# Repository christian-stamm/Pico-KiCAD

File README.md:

# Pico-KiCAD

The **DebugProbe** project aims to re-imagine Raspberry Pi Debug Probe.

## Anke (Debug Probe)

**Anke** is a 4-layer board intended to accommodate the popular Raspberry Pi RP2040 MCU with all required component to function identically to Raspberry Pi Debug Probe. The board is pin-compatible with Raspberry Pi Debug Probe and can be used with the same picoprobe SW.

Features:

- Very small form-factor of about 25x40mm.
- Raspberry Pi RP2040 MCU as a heart of the board.
- USB Type-C connector for power and communication.
- Several LEDs to indicate power and status.
- BOOTSEL button to enter the bootloader mode for flashing new picoprobe SW.
- Pin-compatible with Raspberry Pi Debug Probe.

## Bernd (RGB Panel ECU)

Bernd is a 4-layer board intended to drive 4x2 RGB Panels each consisting of 64x64 Pixel.

Features:

- Very small form-factor of about 60x60mm.
- Raspberry Pi RP2350B MCU as a heart of the board.
- USB Type-C connector for power and communication.
- BOOTSEL button to enter the bootloader mode for flashing new picoprobe SW.

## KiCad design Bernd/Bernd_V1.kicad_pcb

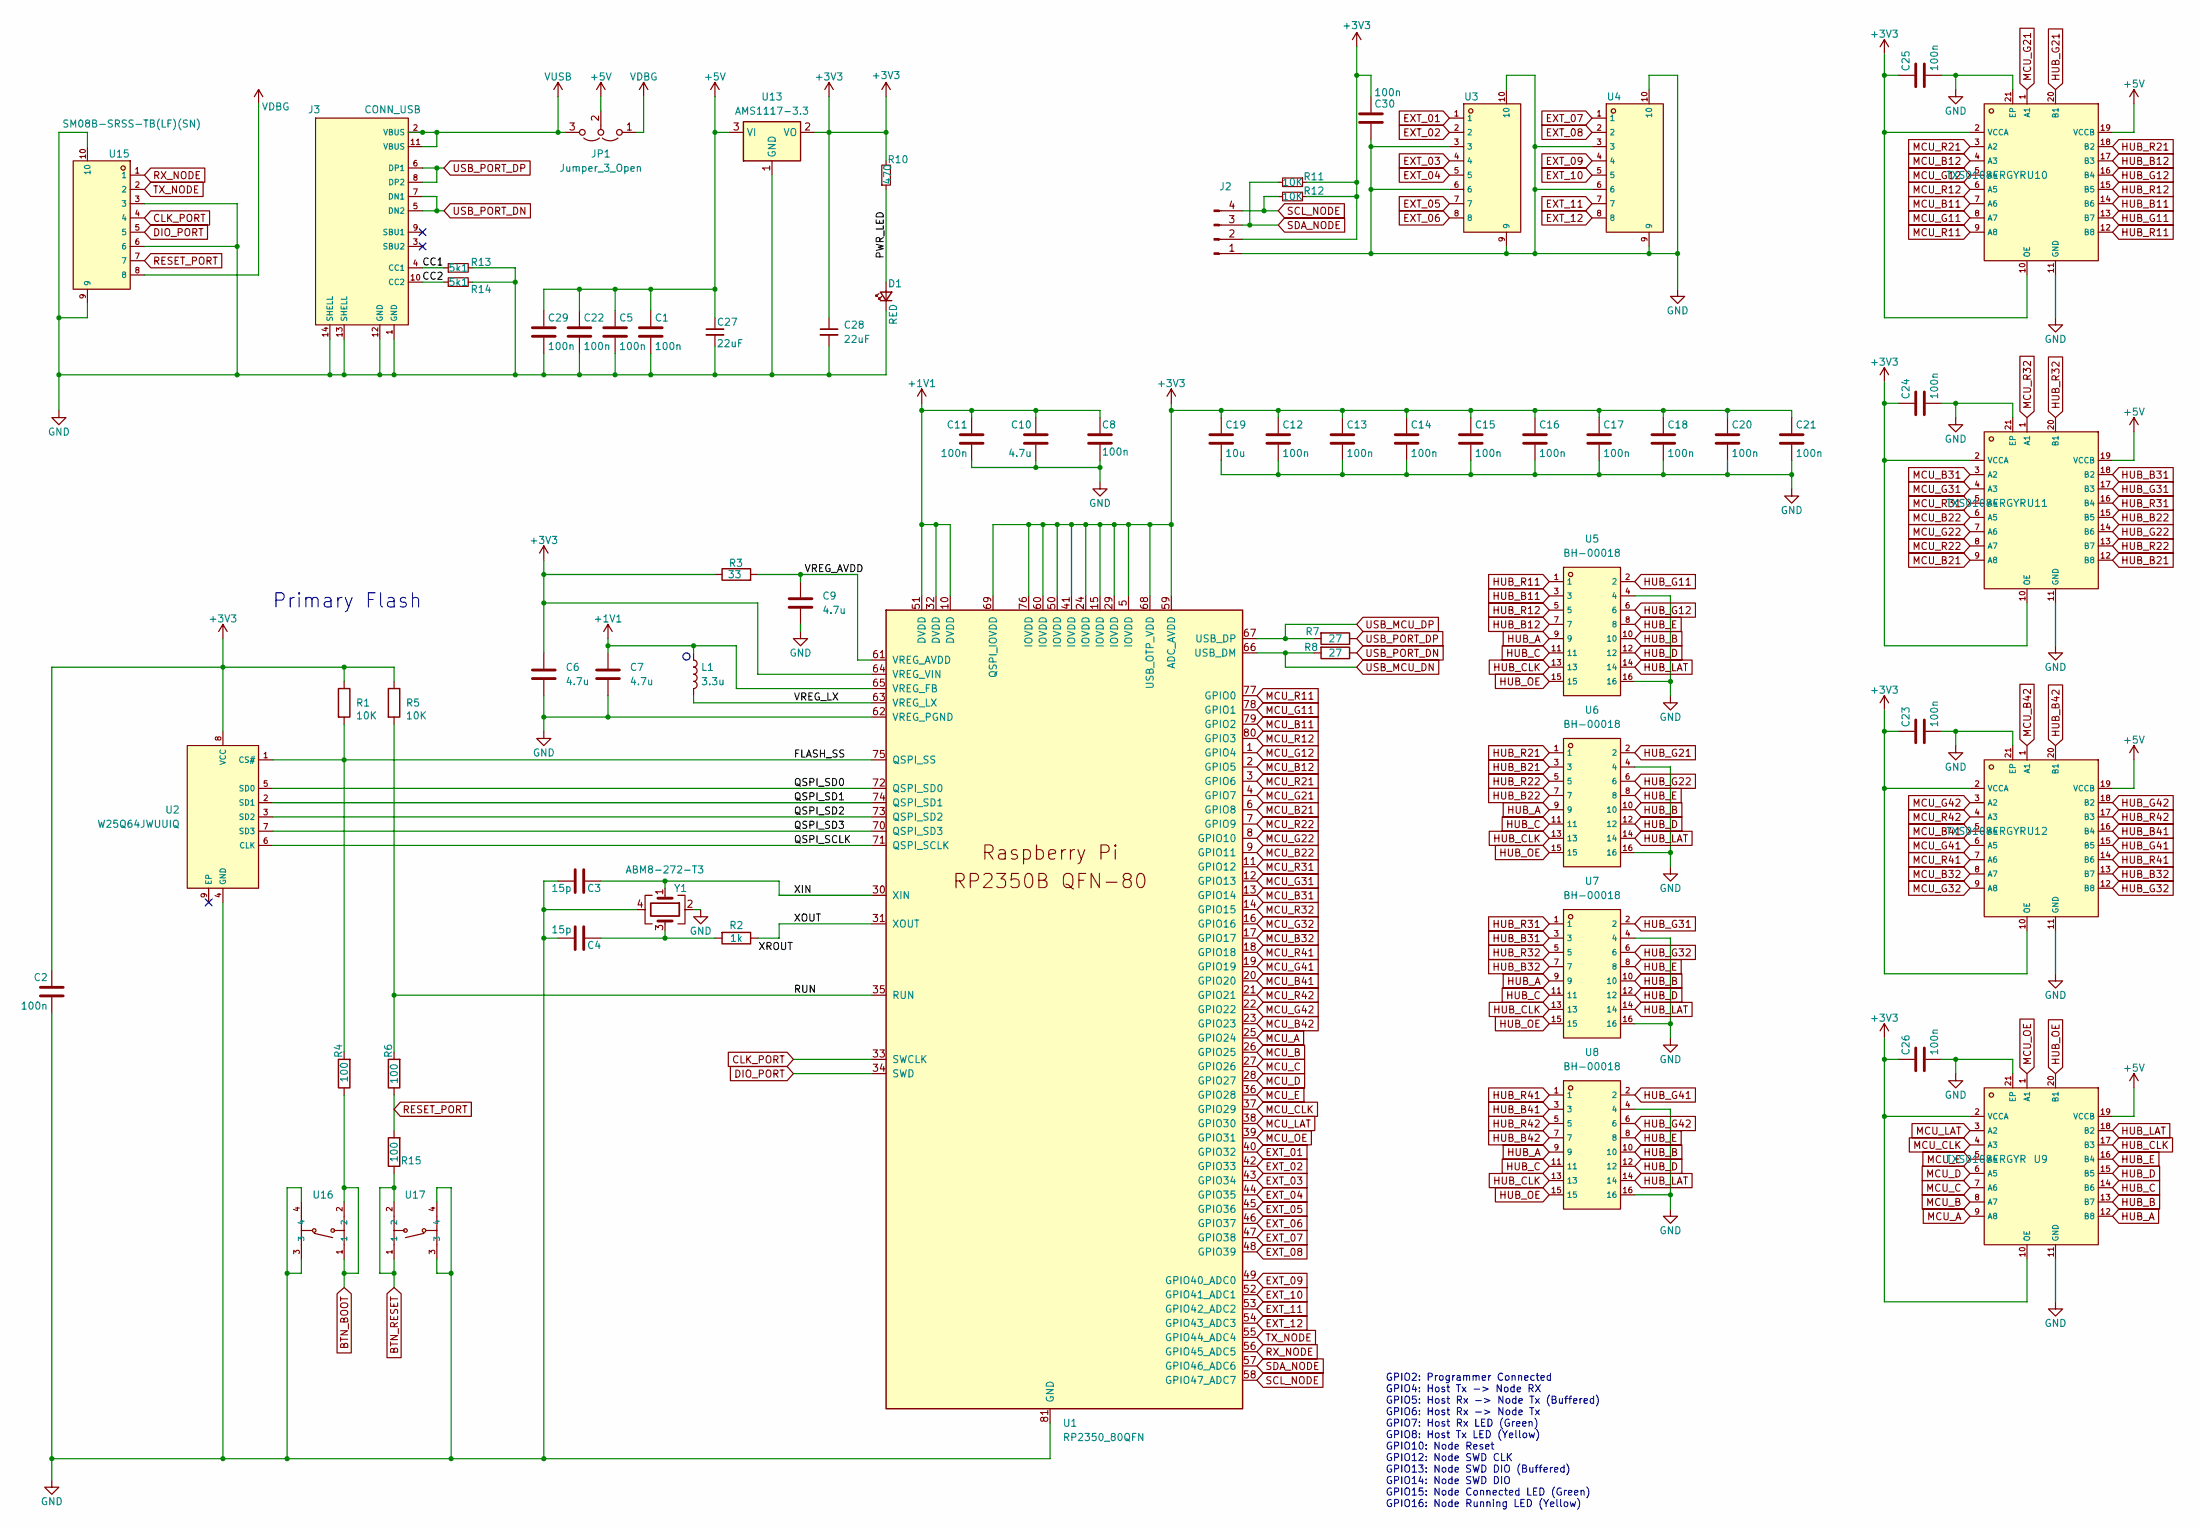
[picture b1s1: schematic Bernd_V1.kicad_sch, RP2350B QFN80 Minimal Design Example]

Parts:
C1, C2, C5, C8, C11, C12, C13, C14, C15, C16, C17, C18, C20, C21, C22, C23, C24, C25, C26, C29, C30: 100n; C_0402_1005Metric
C3, C4: 15p; C_0402_1005Metric
C6, C7: 4.7u; R_0402_1005Metric
C9, C10: 4.7u; C_0402_1005Metric
C19: 10u; C_0402_1005Metric
C27, C28: 22uF; C_0603_1608Metric; LCSC C45783
D1: RED; LED_0603_1608Metric; LCSC C2286
J2: Conn_01x04_Pin; JST_SH_BM04B-SRSS-TB_1x04-1MP_P1.00mm_Vertical; LCSC C160390
J3: CONN_USB; USB-C-SMD_TYPE-C-6PIN-2MD-073; LCSC C2765186
JP1: Jumper_3_Open; PinHeader_1x03_P2.54mm_Vertical_SMD_Pin1Left
L1: 3.3u; IND-SMD_L2.0-W1.6_AOTA-B201610S3R3-101-T
R1, R5: 10K; R_0402_1005Metric
R2: 1k; R_0402_1005Metric
R3: 33; R_0402_1005Metric
R4, R6, R15: 100; R_0402_1005Metric
R7, R8: 27; R_0402_1005Metric
R10: 470; R_0402_1005Metric; LCSC C11702
R11, R12: 10K; R_0402_1005Metric; LCSC C11702
R13, R14: 5k1; R_0402_1005Metric; LCSC C25905
U1: RP2350_80QFN; QFN-80_L10.0-W10.0-P0.40-TL-EP3.4
U2: W25Q64JWUUIQ; USON-8_L3.0-W2.0-P0.50-BL-EP; LCSC C6604692
U3, U4, U15: SM08B-SRSS-TB(LF)(SN); CONN-TH_SM08B-SRSS-TB-LF-SN; LCSC C160407
U5, U6, U7, U8: BH-00018; CONN-SMD_321016MG0CBK00A0; LCSC C2829931
U9, U10, U11, U12: TXS0108ERGYR; VQFN-20_L4.6-W3.6-P0.50-BL-EP; LCSC C90706
U13: AMS1117-3.3; SOT-223-3_TabPin2
U16, U17: TS-1089S-02526; SW-SMD_4P-L4.2-W3.3-P2.15-LS5.1; LCSC C455282
Y1: ABM8-272-T3; CRYSTAL-SMD_4P-L3.2-W2.5-BL

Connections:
+1V1: C7.1, C8.1, C10.1, C11.1, L1.1, U1.10 (DVDD), U1.32 (DVDD), U1.51 (DVDD), U1.65 (VREG_FB)
+3V3: C2.1, C6.1, C12.1, C13.1, C14.1, C15.1, C16.1, C17.1, C18.1, C19.1, C20.1, C21.1, C23.1, C24.1, C25.1, C26.1, C28.1, C30.1, J2.2, R1.1, R3.1, R5.1, R10.2, R11.1, R12.1, U1.5 (IOVDD), U1.15 (IOVDD), U1.24 (IOVDD), U1.29 (IOVDD), U1.41 (IOVDD), U1.50 (IOVDD), U1.59 (ADC_AVDD), U1.60 (IOVDD), U1.64 (VREG_VIN), U1.68 (USB_OTP_VDD), U1.69 (QSPI_IOVDD), U1.76 (IOVDD), U2.8 (VCC), U9.2 (VCCA), U9.10 (OE), U10.2 (VCCA), U10.10 (OE), U11.2 (VCCA), U11.10 (OE), U12.2 (VCCA), U12.10 (OE), U13.2 (VO)
+5V: C1.1, C5.1, C22.1, C27.1, C29.1, JP1.2 (C), U9.19 (VCCB), U10.19 (VCCB), U11.19 (VCCB), U12.19 (VCCB), U13.3 (VI)
/CC1: J3.4 (CC1), R13.1
/CC2: J3.10 (CC2), R14.1
/FLASH_SS: R1.2, R4.2, U1.75 (QSPI_SS), U2.1 (CS#)
/PWR_LED: D1.2 (A), R10.1
/QSPI_SCLK: U1.71 (QSPI_SCLK), U2.6 (CLK)
/QSPI_SD0: U1.72 (QSPI_SD0), U2.5 (SD0)
/QSPI_SD1: U1.74 (QSPI_SD1), U2.2 (SD1)
/QSPI_SD2: U1.73 (QSPI_SD2), U2.3 (SD2)
/QSPI_SD3: U1.70 (QSPI_SD3), U2.7 (SD3)
/RUN: R5.2, R6.2, U1.35 (RUN)
/VREG_AVDD: C9.1, R3.2, U1.61 (VREG_AVDD)
/VREG_LX: L1.2, U1.63 (VREG_LX)
/XIN: C3.1, U1.30 (XIN), Y1.1
/XOUT: R2.1, U1.31 (XOUT)
BTN_BOOT: R4.1, U16.1, U16.2
BTN_RESET: R15.1, U17.1, U17.2
CLK_PORT: U1.33 (SWCLK), U15.4
DIO_PORT: U1.34 (SWD), U15.5
EXT_01: U1.40 (GPIO32), U3.1
EXT_02: U1.42 (GPIO33), U3.2
EXT_03: U1.43 (GPIO34), U3.4
EXT_04: U1.44 (GPIO35), U3.5
EXT_05: U1.45 (GPIO36), U3.7
EXT_06: U1.46 (GPIO37), U3.8
EXT_07: U1.47 (GPIO38), U4.1
EXT_08: U1.48 (GPIO39), U4.2
EXT_09: U1.49 (GPIO40_ADC0), U4.4
EXT_10: U1.52 (GPIO41_ADC1), U4.5
EXT_11: U1.53 (GPIO42_ADC2), U4.7
EXT_12: U1.54 (GPIO43_ADC3), U4.8
GND: C1.2, C2.2, C3.2, C4.2, C5.2, C6.2, C7.2, C8.2, C9.2, C10.2, C11.2, C12.2, C13.2, C14.2, C15.2, C16.2, C17.2, C18.2, C19.2, C20.2, C21.2, C22.2, C23.2, C24.2, C25.2, C26.2, C27.2, C28.2, C29.2, C30.2, D1.1 (K), J2.1, J3.1 (GND), J3.12 (GND), J3.13 (SHELL), J3.14 (SHELL), R13.2, R14.2, U1.62 (VREG_PGND), U1.81 (GND), U2.4 (GND), U3.3, U3.6, U3.9, U3.10, U4.3, U4.6, U4.9, U4.10, U5.4, U5.16, U6.4, U6.16, U7.4, U7.16, U8.4, U8.16, U9.11 (GND), U9.21 (EP), U10.11 (GND), U10.21 (EP), U11.11 (GND), U11.21 (EP), U12.11 (GND), U12.21 (EP), U13.1 (GND), U15.3, U15.6, U15.9, U15.10, U16.3, U16.4, U17.3, U17.4, Y1.2, Y1.4
HUB_A: U5.9, U6.9, U7.9, U8.9, U9.12 (B8)
HUB_B: U5.10, U6.10, U7.10, U8.10, U9.13 (B7)
HUB_B11: U5.3, U10.14 (B6)
HUB_B12: U5.7, U10.17 (B3)
HUB_B21: U6.3, U11.12 (B8)
HUB_B22: U6.7, U11.15 (B5)
HUB_B31: U7.3, U11.18 (B2)
HUB_B32: U7.7, U12.13 (B7)
HUB_B41: U8.3, U12.16 (B4)
HUB_B42: U8.7, U12.20 (B1)
HUB_C: U5.11, U6.11, U7.11, U8.11, U9.14 (B6)
HUB_CLK: U5.13, U6.13, U7.13, U8.13, U9.17 (B3)
HUB_D: U5.12, U6.12, U7.12, U8.12, U9.15 (B5)
HUB_E: U5.8, U6.8, U7.8, U8.8, U9.16 (B4)
HUB_G11: U5.2, U10.13 (B7)
HUB_G12: U5.6, U10.16 (B4)
HUB_G21: U6.2, U10.20 (B1)
HUB_G22: U6.6, U11.14 (B6)
HUB_G31: U7.2, U11.17 (B3)
HUB_G32: U7.6, U12.12 (B8)
HUB_G41: U8.2, U12.15 (B5)
HUB_G42: U8.6, U12.18 (B2)
HUB_LAT: U5.14, U6.14, U7.14, U8.14, U9.18 (B2)
HUB_OE: U5.15, U6.15, U7.15, U8.15, U9.20 (B1)
HUB_R11: U5.1, U10.12 (B8)
HUB_R12: U5.5, U10.15 (B5)
HUB_R21: U6.1, U10.18 (B2)
HUB_R22: U6.5, U11.13 (B7)
HUB_R31: U7.1, U11.16 (B4)
HUB_R32: U7.5, U11.20 (B1)
HUB_R41: U8.1, U12.14 (B6)
HUB_R42: U8.5, U12.17 (B3)
MCU_A: U1.25 (GPIO24), U9.9 (A8)
MCU_B: U1.26 (GPIO25), U9.8 (A7)
MCU_B11: U1.79 (GPIO2), U10.7 (A6)
MCU_B12: U1.2 (GPIO5), U10.4 (A3)
MCU_B21: U1.6 (GPIO8), U11.9 (A8)
MCU_B22: U1.9 (GPIO11), U11.6 (A5)
MCU_B31: U1.13 (GPIO14), U11.3 (A2)
MCU_B32: U1.17 (GPIO17), U12.8 (A7)
MCU_B41: U1.20 (GPIO20), U12.5 (A4)
MCU_B42: U1.23 (GPIO23), U12.1 (A1)
MCU_C: U1.27 (GPIO26), U9.7 (A6)
MCU_CLK: U1.37 (GPIO29), U9.4 (A3)
MCU_D: U1.28 (GPIO27), U9.6 (A5)
MCU_E: U1.36 (GPIO28), U9.5 (A4)
MCU_G11: U1.78 (GPIO1), U10.8 (A7)
MCU_G12: U1.1 (GPIO4), U10.5 (A4)
MCU_G21: U1.4 (GPIO7), U10.1 (A1)
MCU_G22: U1.8 (GPIO10), U11.7 (A6)
MCU_G31: U1.12 (GPIO13), U11.4 (A3)
MCU_G32: U1.16 (GPIO16), U12.9 (A8)
MCU_G41: U1.19 (GPIO19), U12.6 (A5)
MCU_G42: U1.22 (GPIO22), U12.3 (A2)
MCU_LAT: U1.38 (GPIO30), U9.3 (A2)
MCU_OE: U1.39 (GPIO31), U9.1 (A1)
MCU_R11: U1.77 (GPIO0), U10.9 (A8)
MCU_R12: U1.80 (GPIO3), U10.6 (A5)
MCU_R21: U1.3 (GPIO6), U10.3 (A2)
MCU_R22: U1.7 (GPIO9), U11.8 (A7)
MCU_R31: U1.11 (GPIO12), U11.5 (A4)
MCU_R32: U1.14 (GPIO15), U11.1 (A1)
MCU_R41: U1.18 (GPIO18), U12.7 (A6)
MCU_R42: U1.21 (GPIO21), U12.4 (A3)
unnamed: C4.1, R2.2, Y1.3
RESET_PORT: R6.1, R15.2, U15.7
RX_NODE: U1.56 (GPIO45_ADC5), U15.1
SCL_NODE: J2.4, R12.2, U1.58 (GPIO47_ADC7)
SDA_NODE: J2.3, R11.2, U1.57 (GPIO46_ADC6)
TX_NODE: U1.55 (GPIO44_ADC4), U15.2
USB_MCU_DN: R8.2, U1.66 (USB_DM)
USB_MCU_DP: R7.2, U1.67 (USB_DP)
USB_PORT_DN: J3.5 (DN2), J3.7 (DN1), R8.1
USB_PORT_DP: J3.6 (DP1), J3.8 (DP2), R7.1
VDBG: JP1.1 (A), U15.8
VUSB: J3.2 (VBUS), J3.11 (VBUS), JP1.3 (B)

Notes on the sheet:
Primary Flash
GPIO2: Programmer Connected GPIO4: Host Tx -> Node RX GPIO5: Host Rx -> Node Tx (Buffered) GPIO6: Host Rx -> Node Tx GPIO7: Host Rx LED (Green) GPIO8: Host Tx LED (Yellow) GPIO10: Node Reset GPIO12: Node SWD CLK GPIO13: Node SWD DIO (Buffered) GPIO14: Node SWD DIO GPIO15: Node Connected LED (Green)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

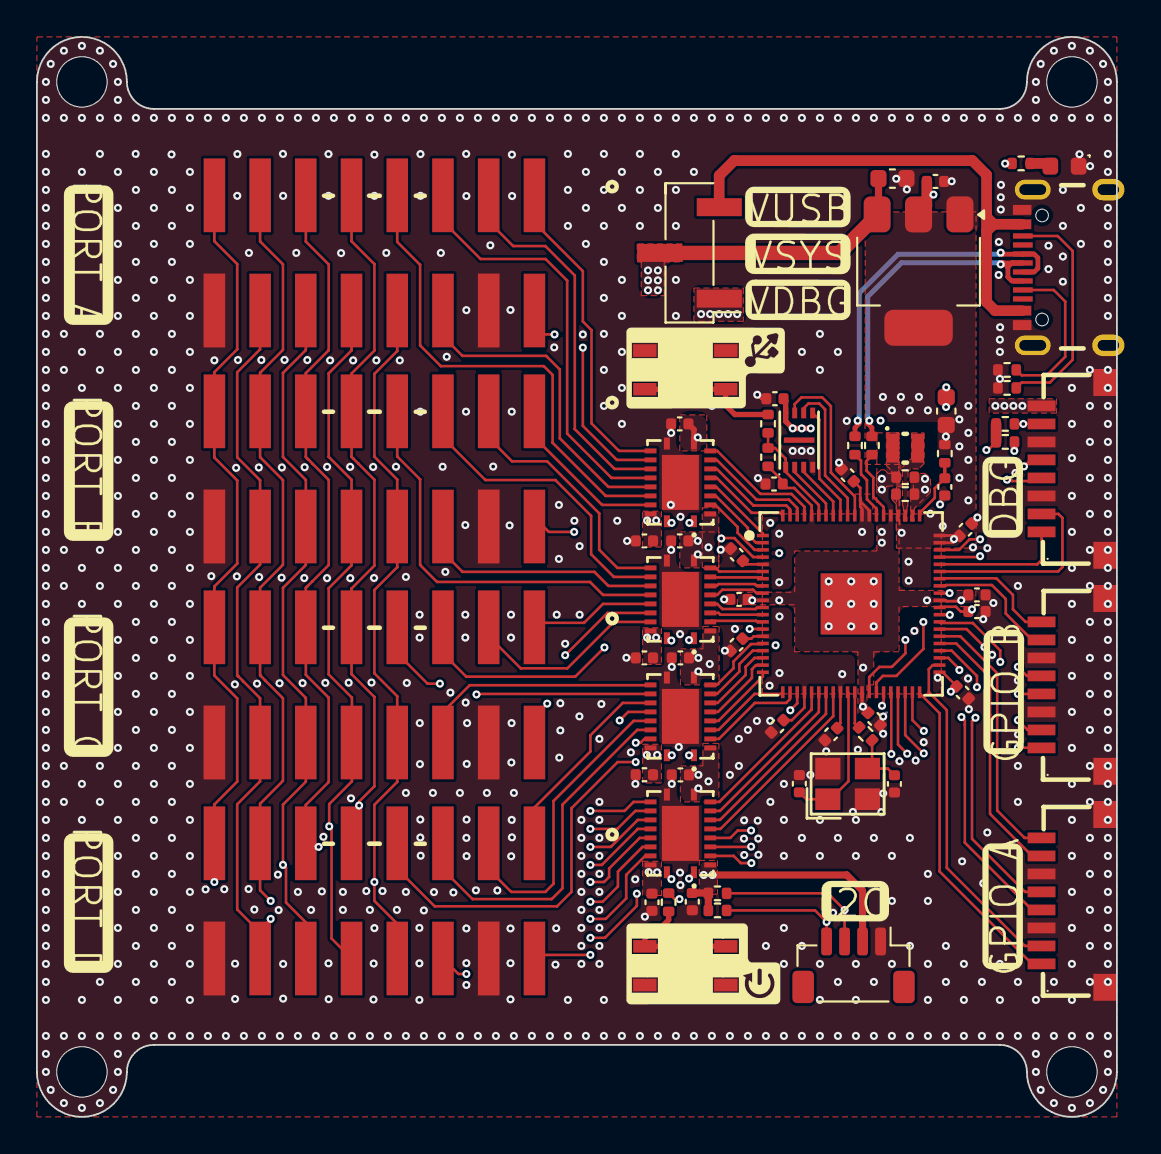
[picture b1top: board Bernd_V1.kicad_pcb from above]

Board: 4 copper layers, 60.0 x 60.0 mm, 66 parts (0 on the bottom side), 110 nets.

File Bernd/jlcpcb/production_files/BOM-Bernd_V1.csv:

Comment,Designator,Footprint,LCSC,Quantity
470,"R10,R11,R12,R2",R_0402_1005Metric,C11702,4
100n,"C1,C11,C12,C13,C14,C15,C16,C17,C18,C2,C20,C21,C22,C23,C24,C25,C26,C29,C30,C5,C8",C_0402_1005Metric,C1525,21
15p,"C3,C4",C_0402_1005Metric,C1548,2
10u,C19,C_0402_1005Metric,C15525,1
Conn_01x04_Pin,J2,JST_SH_BM04B-SRSS-TB_1x04-1MP_P1.00mm_Vertical,C160390,1
SM08B-SRSS-TB(LF)(SN),"U15,U3,U4",CONN-TH_SM08B-SRSS-TB-LF-SN,C160407,3
ABM8-272-T3,Y1,CRYSTAL-SMD_4P-L3.2-W2.5-BL,C20625731,1
RED,D1,LED_0603_1608Metric,C2286,1
4.7u,"C10,C6,C7,C9",C_0402_1005Metric,C23733,4
100,"R15,R4,R6",R_0402_1005Metric,C25076,3
33,R3,R_0402_1005Metric,C25105,1
10K,"R1,R5",R_0402_1005Metric,C25744,2
5k1,"R13,R14",R_0402_1005Metric,C25905,2
CONN_USB,J3,USB-C-SMD_TYPE-C-6PIN-2MD-073,C2765186,1
BH-00018,"U5,U6,U7,U8",CONN-SMD_321016MG0CBK00A0,C2829931,4
3.3u,L1,IND-SMD_L2.0-W1.6_AOTA-B201610S3R3-101-T,C42411119,1
RP2350_80QFN,U1,QFN-80_L10.0-W10.0-P0.40-TL-EP3.4,C42415655,1
TS-1089S-02526,"U16,U17",SW-SMD_4P-L4.2-W3.3-P2.15-LS5.1,C455282,2
22uF,"C27,C28",C_0603_1608Metric,C45783,2
27,"R7,R8",R_0402_1005Metric,C5151586,2
Jumper_3_Open,JP1,PinHeader_1x03_P2.54mm_Vertical_SMD_Pin1Left,C5967212,1
AMS1117-3.3,U13,SOT-223-3_TabPin2,C6186,1
W25Q64JWUUIQ,U2,USON-8_L3.0-W2.0-P0.50-BL-EP,C6604692,1
TXS0108ERGYR,"U10,U11,U12,U9",VQFN-20_L4.6-W3.6-P0.50-BL-EP,C90706,4

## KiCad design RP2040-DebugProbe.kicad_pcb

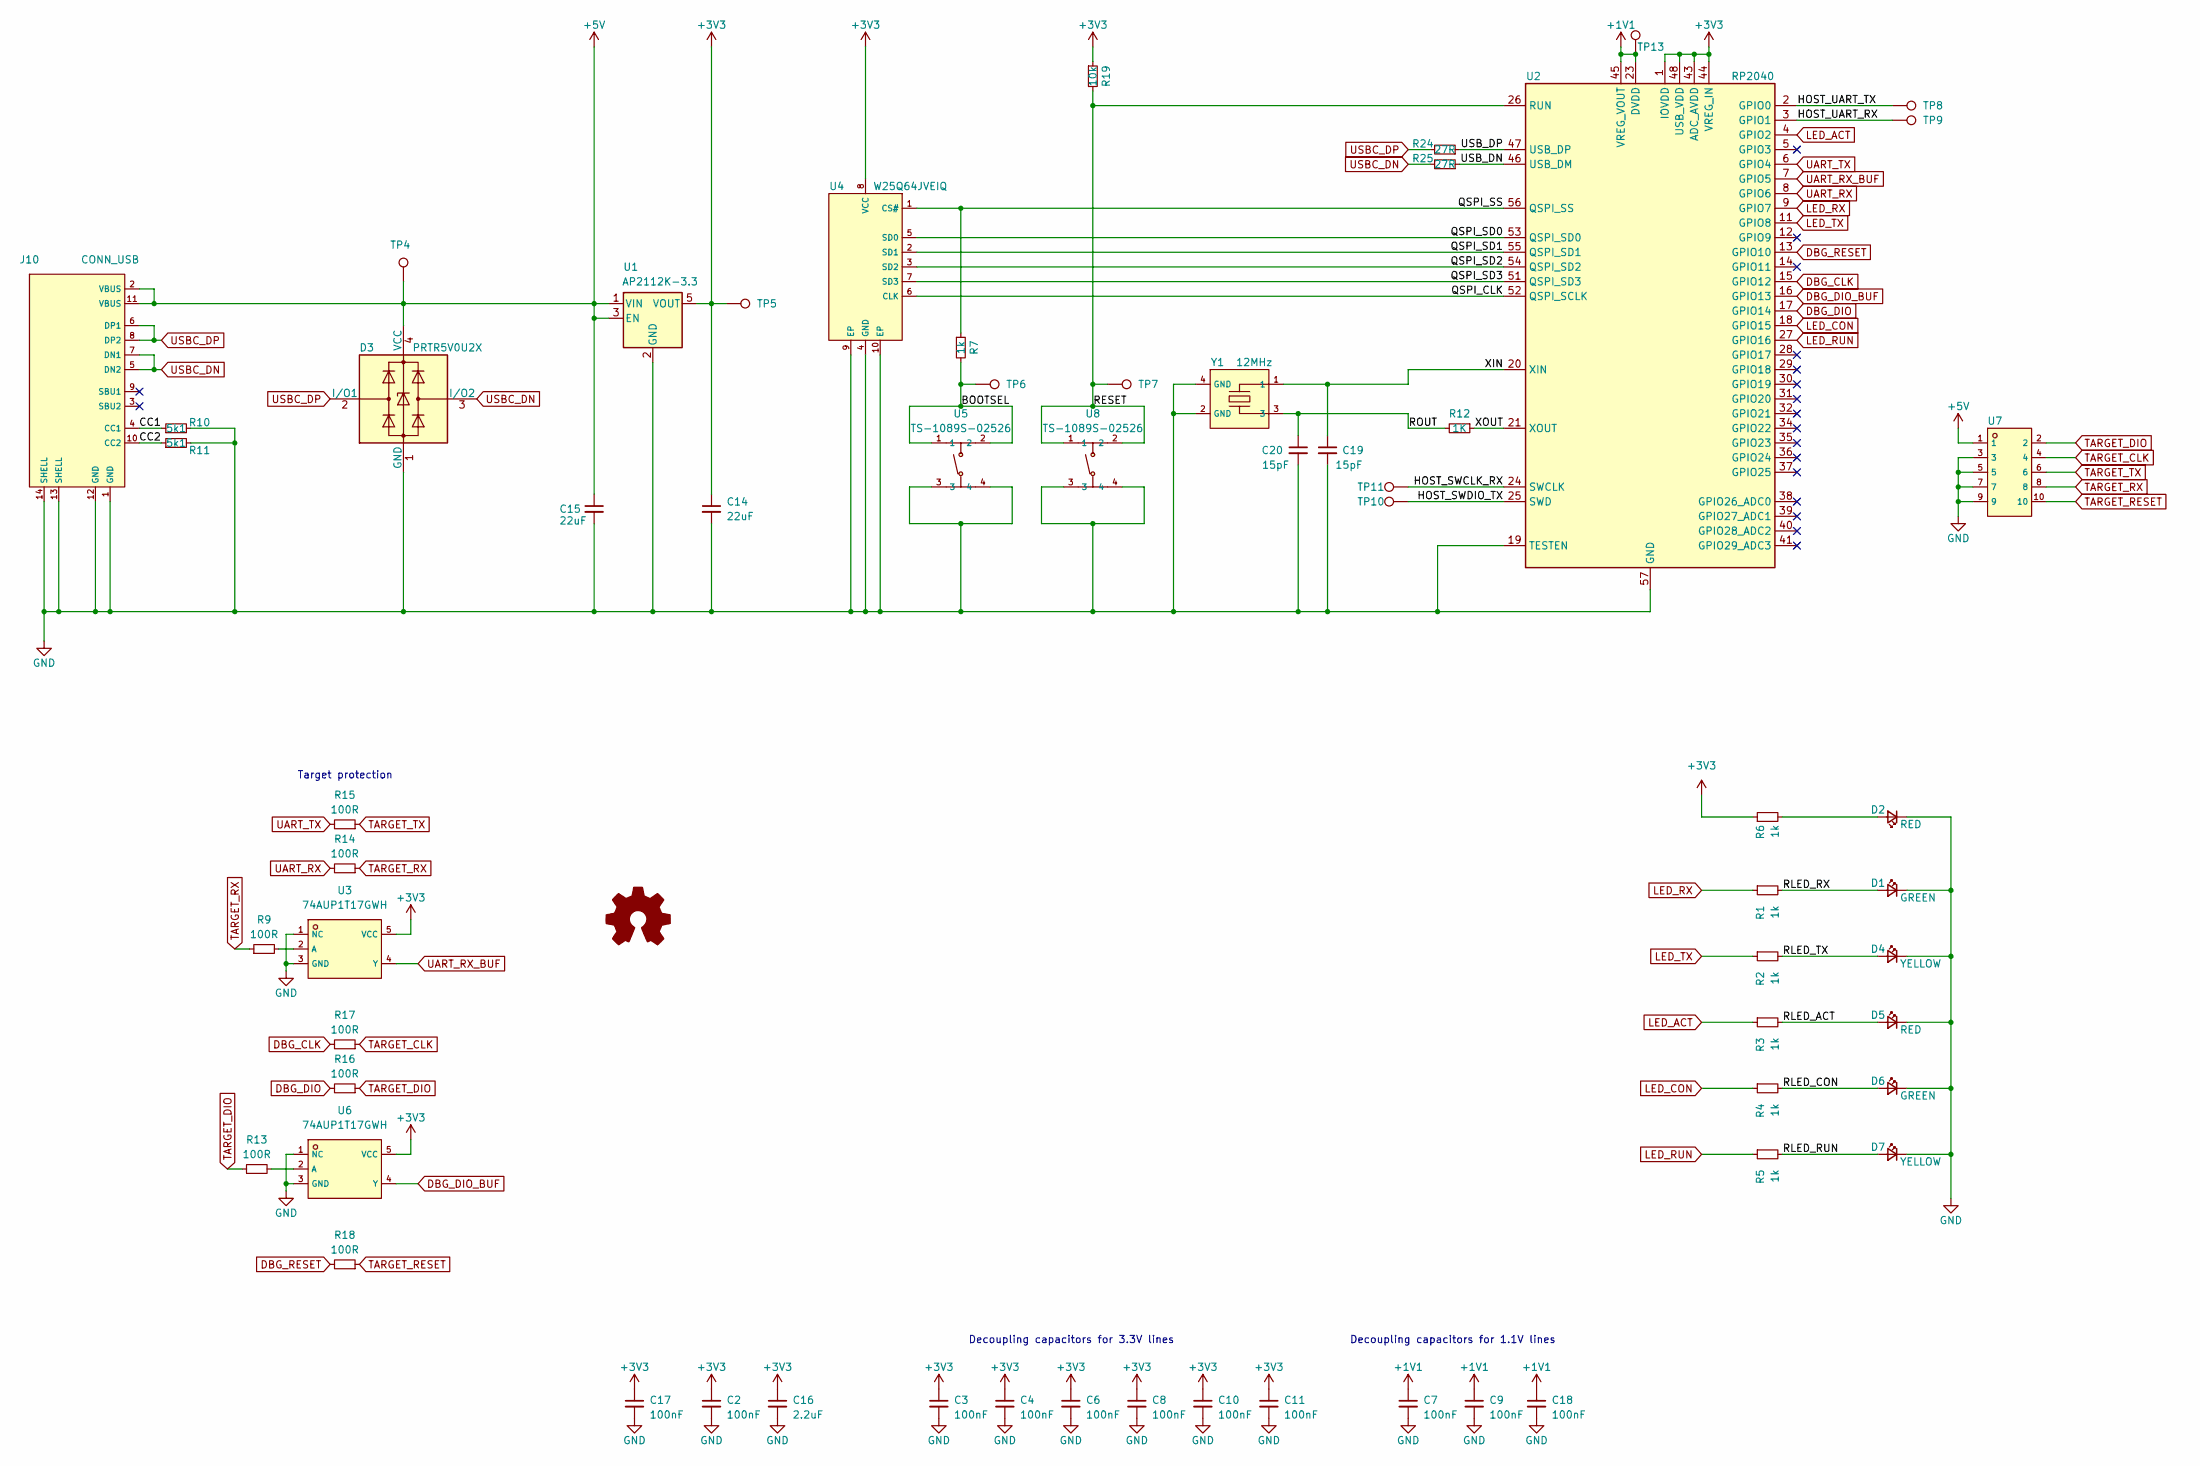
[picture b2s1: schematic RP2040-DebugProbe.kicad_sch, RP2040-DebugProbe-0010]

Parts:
C2, C3, C4, C6, C7, C8, C9, C10, C11, C17, C18: 100nF; C_0402_1005Metric
C14, C15: 22uF; C_0805_2012Metric
C16: 2.2uF; C_0603_1608Metric
C19, C20: 15pF; C_0402_1005Metric
D1, D6: GREEN; LED_0603_1608Metric
D2, D5: RED; LED_0603_1608Metric
D3: PRTR5V0U2X; SOT-143
D4, D7: YELLOW; LED_0603_1608Metric
J10: CONN_USB; USB-C-SMD_TYPE-C-6PIN-2MD-073; LCSC C2765186
R1, R2, R3, R4, R5, R6, R7: 1k; R_0402_1005Metric
R9, R13, R14, R15, R16, R17, R18: 100R; R_0402_1005Metric
R10, R11: 5k1; R_0402_1005Metric
R12: 1K; R_0402_1005Metric
R19: 10k; R_0402_1005Metric
R24, R25: 27R; R_0402_1005Metric
TP4, TP5, TP6, TP7, TP8, TP9, TP10, TP11, TP13: TestPoint; TestPoint_Pad_1.0x1.0mm
U1: AP2112K-3.3; SOT-23-5
U2: RP2040; QFN-56-1EP_7x7mm_P0.4mm_EP3.2x3.2mm
U3, U6: 74AUP1T17GWH; TSSOP-5_L2.1-W1.3-P0.65-LS2.2-BR; LCSC C545951
U4: W25Q64JVEIQ; USON-8_L4.0-W3.0-P0.80-BL_WINBOND_UU; LCSC C6604692
U5, U8: TS-1089S-02526; SW-SMD_4P-L4.2-W3.3-P2.15-LS5.1; LCSC C455282
U7: HX_JN1_27-2X5_TP_H4_9; IDC-SMD_10P-P1.27-3220-10-0300-00; LCSC C42372555
Y1: 12MHz; CRYSTAL-SMD_4P-L3.2-W2.5-BL; LCSC C20625731

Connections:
+1V1: C7.1, C9.1, C18.1, TP13.1, U2.23 (DVDD), U2.45 (VREG_VOUT), U2.50 (DVDD)
+3V3: C2.1, C3.1, C4.1, C6.1, C8.1, C10.1, C11.1, C14.1, C16.1, C17.1, R6.1, R19.1, TP5.1, U1.5 (VOUT), U2.1 (IOVDD), U2.10 (IOVDD), U2.22 (IOVDD), U2.33 (IOVDD), U2.42 (IOVDD), U2.43 (ADC_AVDD), U2.44 (VREG_IN), U2.48 (USB_VDD), U2.49 (IOVDD), U3.5 (VCC), U4.8 (VCC), U6.5 (VCC)
+5V: C15.1, D3.4 (VCC), J10.2 (VBUS), J10.11 (VBUS), TP4.1, U1.1 (VIN), U1.3 (EN), U7.1
/BOOTSEL: R7.2, TP6.1, U5.1, U5.2
/CC1: J10.4 (CC1), R10.1
/CC2: J10.10 (CC2), R11.1
/HOST_SWCLK_RX: TP11.1, U2.24 (SWCLK)
/HOST_SWDIO_TX: TP10.1, U2.25 (SWD)
/HOST_UART_RX: TP9.1, U2.3 (GPIO1)
/HOST_UART_TX: TP8.1, U2.2 (GPIO0)
/QSPI_CLK: U2.52 (QSPI_SCLK), U4.6 (CLK)
/QSPI_SD0: U2.53 (QSPI_SD0), U4.5 (SD0)
/QSPI_SD1: U2.55 (QSPI_SD1), U4.2 (SD1)
/QSPI_SD2: U2.54 (QSPI_SD2), U4.3 (SD2)
/QSPI_SD3: U2.51 (QSPI_SD3), U4.7 (SD3)
/QSPI_SS: R7.1, U2.56 (QSPI_SS), U4.1 (CS#)
/RESET: R19.2, TP7.1, U2.26 (RUN), U8.1, U8.2
/RLED_ACT: D5.2 (A), R3.2
/RLED_CON: D6.2 (A), R4.2
/RLED_RUN: D7.2 (A), R5.2
/RLED_RX: D1.2 (A), R1.2
/RLED_TX: D4.2 (A), R2.2
/ROUT: C20.1, R12.2, Y1.3
/USB_DN: R25.1, U2.46 (USB_DM)
/USB_DP: R24.1, U2.47 (USB_DP)
/XIN: C19.1, U2.20 (XIN), Y1.1
/XOUT: R12.1, U2.21 (XOUT)
DBG_CLK: R17.2, U2.15 (GPIO12)
DBG_DIO: R16.2, U2.17 (GPIO14)
DBG_DIO_BUF: U2.16 (GPIO13), U6.4 (Y)
DBG_RESET: R18.2, U2.13 (GPIO10)
GND: C2.2, C3.2, C4.2, C6.2, C7.2, C8.2, C9.2, C10.2, C11.2, C14.2, C15.2, C16.2, C17.2, C18.2, C19.2, C20.2, D1.1 (K), D2.1 (K), D3.1 (GND), D4.1 (K), D5.1 (K), D6.1 (K), D7.1 (K), J10.1 (GND), J10.12 (GND), J10.13 (SHELL), J10.14 (SHELL), R10.2, R11.2, U1.2 (GND), U2.19 (TESTEN), U2.57 (GND), U3.1 (NC), U3.3 (GND), U4.4 (GND), U4.9 (EP), U4.10 (EP), U5.3, U5.4, U6.1 (NC), U6.3 (GND), U7.3, U7.5, U7.7, U7.9, U8.3, U8.4, Y1.2 (GND), Y1.4 (GND)
LED_ACT: R3.1, U2.4 (GPIO2)
LED_CON: R4.1, U2.18 (GPIO15)
LED_RUN: R5.1, U2.27 (GPIO16)
LED_RX: R1.1, U2.9 (GPIO7)
LED_TX: R2.1, U2.11 (GPIO8)
unnamed: D2.2 (A), R6.2
unnamed: R9.2, U3.2 (A)
unnamed: R13.2, U6.2 (A)
TARGET_CLK: R17.1, U7.4
TARGET_DIO: R13.1, R16.1, U7.2
TARGET_RESET: R18.1, U7.10
TARGET_RX: R9.1, R14.1, U7.8
TARGET_TX: R15.1, U7.6
UART_RX: R14.2, U2.8 (GPIO6)
UART_RX_BUF: U2.7 (GPIO5), U3.4 (Y)
UART_TX: R15.2, U2.6 (GPIO4)
USBC_DN: D3.3 (I/O2), J10.5 (DN2), J10.7 (DN1), R25.2
USBC_DP: D3.2 (I/O1), J10.6 (DP1), J10.8 (DP2), R24.2

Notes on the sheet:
Decoupling capacitors for 3.3V lines
Decoupling capacitors for 1.1V lines
Target protection

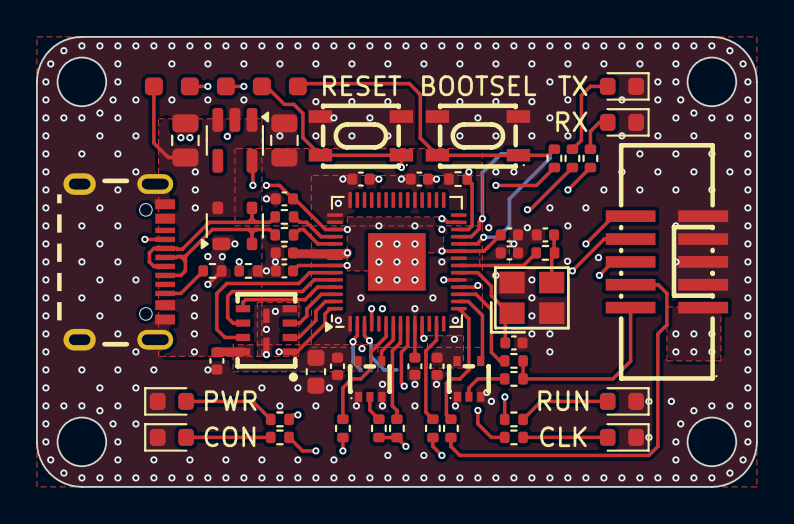
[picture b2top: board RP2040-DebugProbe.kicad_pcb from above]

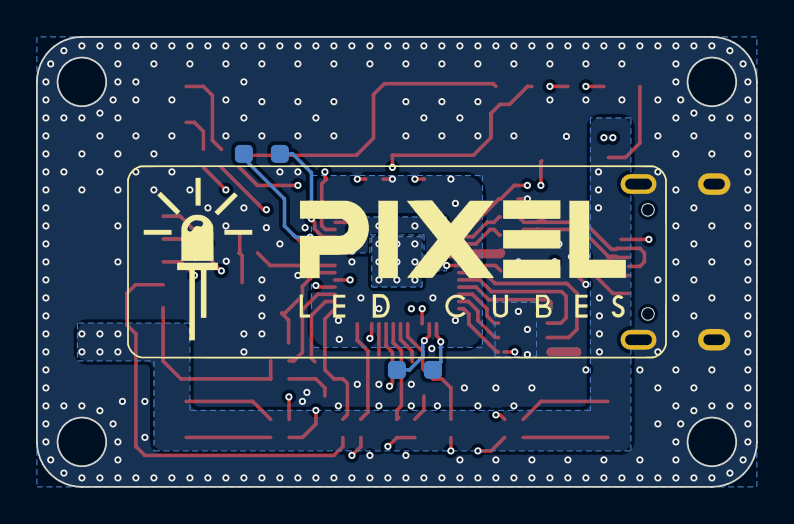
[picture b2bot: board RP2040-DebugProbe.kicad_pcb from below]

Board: 4 copper layers, 40.0 x 25.0 mm, 62 parts (4 on the bottom side), 50 nets.

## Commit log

2025-01-30 init
2025-02-03 tinyprogrammer
2025-02-03 logo
2025-05-21 AnkeV2
2025-05-22 Bernd

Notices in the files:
RP2040-DebugProbe.kicad_pcb:
(c) 2023 Andriy Golovnya
